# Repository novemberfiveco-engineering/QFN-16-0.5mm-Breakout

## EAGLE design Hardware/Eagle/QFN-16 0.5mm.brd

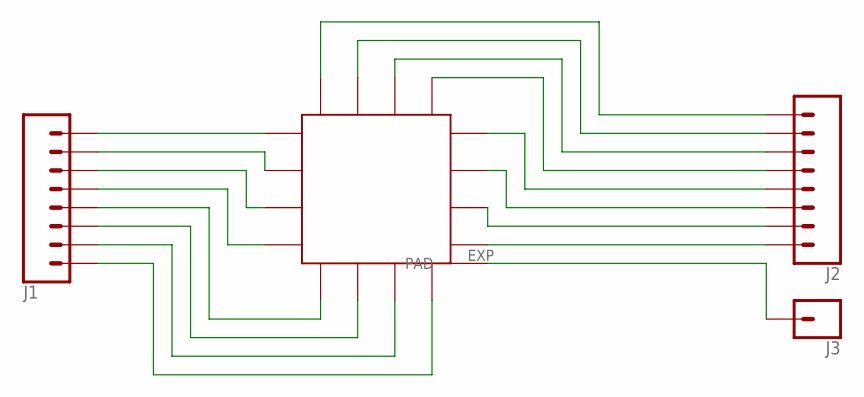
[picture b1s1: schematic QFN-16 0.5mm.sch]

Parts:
J1, J2: CONN_08"; 1X08
J3: CONN_01; 1X01
U$1: QFN-16_0,5MM; QFN16_0,5MM

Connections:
unnamed: J1.1, U$1.1 (PIN1)
unnamed: J1.2, U$1.2 (PIN2)
unnamed: J1.3, U$1.3 (PIN3)
unnamed: J1.4, U$1.4 (PIN4)
unnamed: J1.5, U$1.5 (PIN5)
unnamed: J1.6, U$1.6 (PIN6)
unnamed: J1.7, U$1.7 (PIN7)
unnamed: J1.8, U$1.8 (PIN8)
unnamed: J2.8, U$1.9 (PIN9)
unnamed: J2.7, U$1.10 (PIN10)
unnamed: J2.6, U$1.11 (PIN11)
unnamed: J2.5, U$1.12 (PIN12)
unnamed: J2.4, U$1.13 (PIN13)
unnamed: J2.3, U$1.14 (PIN14)
unnamed: J2.2, U$1.15 (PIN15)
unnamed: J2.1, U$1.16 (PIN16)
unnamed: J3.1, U$1.EXP (PAD)

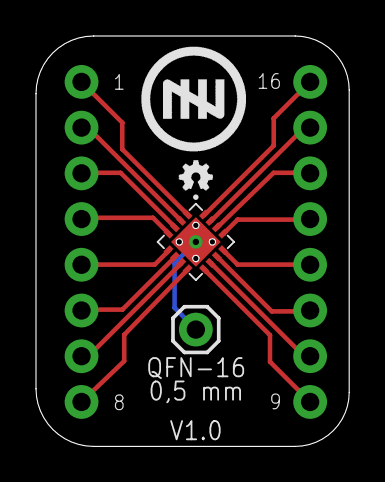
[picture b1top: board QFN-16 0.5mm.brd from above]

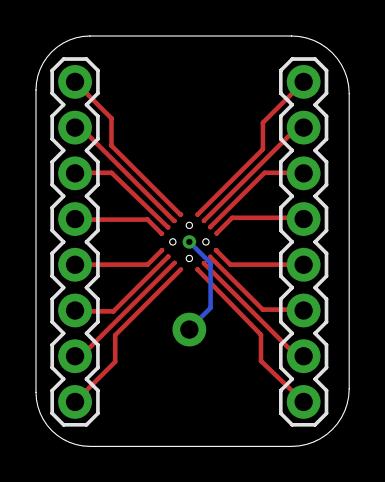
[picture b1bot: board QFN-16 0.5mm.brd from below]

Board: 2 copper layers, 17.4 x 22.8 mm, 6 parts (3 on the bottom side), 17 nets.

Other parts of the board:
U$3: LOGO-OSHWA
U$4: LOGO-NOVEMERFIVE-7SCALE

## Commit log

2017-05-15 Added project library

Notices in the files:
parts and their libraries:
SparkFun-Connectors: Licensing: Creative Commons ShareAlike 4.0 International - https://creativecommons.org/licenses/by-sa/4.0
